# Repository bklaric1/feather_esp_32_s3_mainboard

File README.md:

# feather_esp_32_s3_mainboard

## PCBs for a project at Technical University of Applied Science Augsburg

### Explanation
This repo contains the KiCad 8 files for the main board and the daughter board of the project.  
Necessary files are located in the source folders with the corresponding names, whilst the 3D-models, symbols and footprints can be found in the models, symbols, and footprints folders.  
The rules files are located in the source folders, and correspond with the [2 Layer HD Design Rules](https://community.aisler.net/t/2-layer-hd-design-rules/3732) from Aisler DE.  
The BOM files are located in the source folders in the *bom* folder. They are created using [Interactive HTML Bom](https://github.com/openscopeproject/InteractiveHtmlBom) Plugin. To view the BOM file, clone the repo and open them locally.  
The idea of the design is to make a battery powered system with [Adafruit ESP32-S3 Feather](https://www.adafruit.com/product/5477) as the microcontroller to control the e-paper display. We used the [7.5 inch tri-color electronic paper display](https://www.good-display.com/product/394.html) with the partial refresh as our e-paper display, but any e-paper display from [Good Display](https://www.good-display.com) and from [Waveshare](https://www.waveshare.com) would work, as there is an integrated 3.3V to 5V Boost-Converter which can be turned on if needed (per switch).  
The system is made up from two main PCBs, one that houses the microcontroller and the other which serves as a front panel Board for the buttons.  
All the parts, except the microcontroller, are sponsored by Würth Elektronik. Many thanks to them, as without them sponsoring the parts, the production of the boards would be too expensive for a student project.  
The case for the display, PCBs, and the battery pack are all designed by us and 3D printed.  

### Mainboard
The main board houses the already mentioned Adafruit ESP32-S3 Feather microcontroller. We used the version with 4 MB Flash and 2 MB PSRAM, as we needed the RAM to store a part of firmware on it (static images). The pinout is the same as some other version, so the PCB Design can be used with them as well.  
As already mentioned, there is a 3.3V to 5V Boost-Converter implemented on the board. It is found in the configuration provided by the Würth Elektronik. To switch the output voltage on the display's voltage pin, one needs to only move the switch in another position, as labeled on the board.  
The pinout for the display connector corresponds to the two display manufactures I mentioned above, but check the pinouts before connecting.  
The connector for the board is the connector that links the two boards together.  
Implementation of the external reset button isn't fully finished, but rather left as two pins on the board. I wasn't sure if we'll need to move the reset button somewhere more accessible, so I left it like that. There is no need for another reset button on the board because the microcontroller already features a built-in reset button.  
I also brought the IIC pins out on the board, in case a sensor is need later. These pins are already used internally for the battery monitoring through the MAX17048 chip.  
The battery connection is found directly on the microcontroller module. It is the JST 2-PH plug.  
The microSD adapter is designed by the specification of the espressif themselves, according to their [README](https://github.com/espressif/esp-idf/blob/master/examples/storage/sd_card/sdmmc/README.md). I also fully modified the design to make it possible to switch from the 4-wire connection (SD mode) to the 1-wire connection (SPI), in case we need more GPIO pins for something else.

### Daugtherboard
The design of the daughter board is very simple. It only includes the four buttons with the debouncing design respectively. 
The connector links with the main board to make the system complete.
Board only has one mounting hole, because of the maximum length constrains. We designed the plugin spot for the board on one side, similar to the M.2 SSD mounting technology.

### Battery Pack
As we needed to build a battery powered system, we researched and put together a battery pack with 10 600 mAh and the nominal voltage of 3.7V (4.2V) fully charged.  
The battery pack consists of two 21700 Li-Ion batteries. We have chosen [these](https://www.akkuteile.de/lithium-ionen-akkus/21700/bak/bak-n21700cd-53e-mit-5300mah-10a-3-6v-3-7v-li-ionen-akku_100625_3323) because of the high capacity and small form factor.  
Though any combination of the batteries would work, we decided to maximize the space we have in the case and the budget of our project. That is why we selected these specific cells.  
We also included the already developed [BMS](https://www.akkuteile.de/1s-pcb-keeppower-xzd-1s5530-schutzelektronik-7a_200501_1407) (Battery Management System) PCB to protect the batteries of the deep discharge, overcharge and short circuit.

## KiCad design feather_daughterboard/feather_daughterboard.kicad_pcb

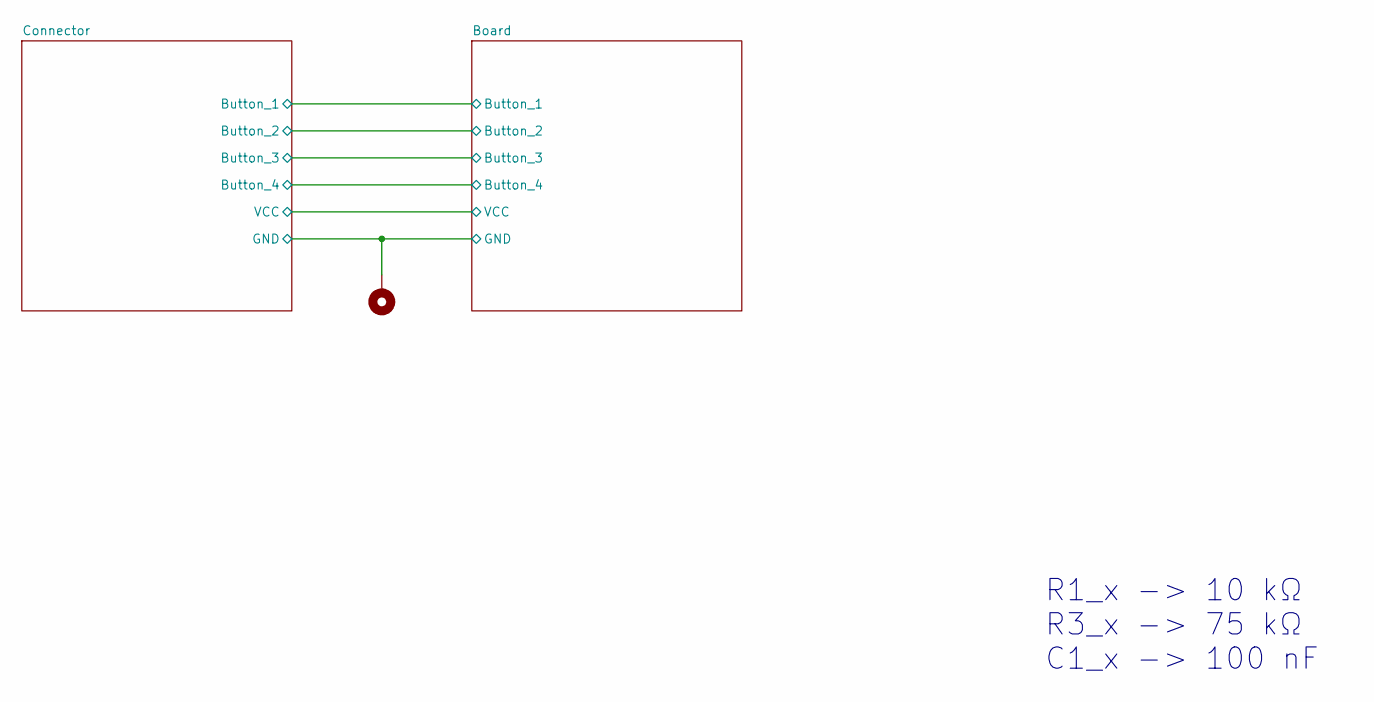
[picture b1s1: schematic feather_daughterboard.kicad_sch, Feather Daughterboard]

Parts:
H2: MountingHole_Pad; MountingHole_2.2mm_M2_DIN965_Pad

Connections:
/Board/GND: H2.1; also elsewhere on the board

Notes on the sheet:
R1_x -> 10 kΩ R3_x -> 75 kΩ C1_x -> 100 nF

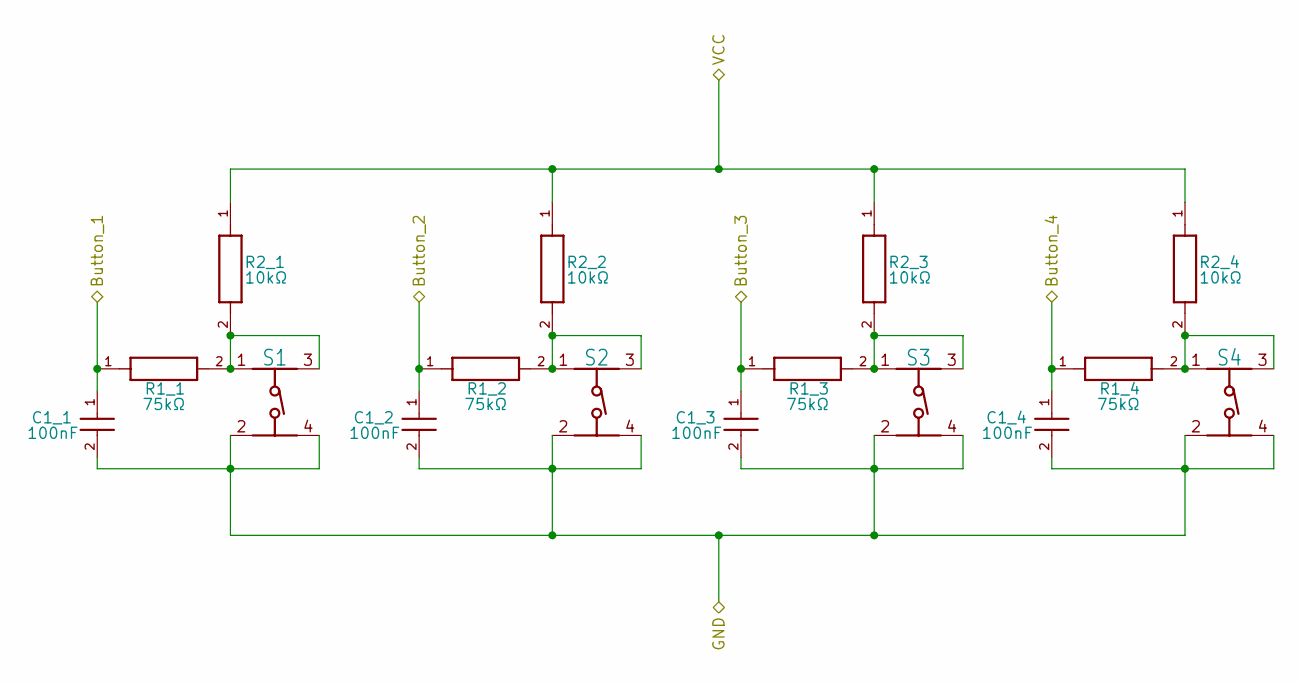
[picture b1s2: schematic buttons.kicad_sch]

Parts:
C1_1, C1_2, C1_3, C1_4: 100nF; WCAP-CSGP_0603_R
R1_1, R1_2, R1_3, R1_4: 75kΩ; WRIS-RSKS_0603_REFLOW
R2_1, R2_2, R2_3, R2_4: 10kΩ; WRIS-RSKS_0603_REFLOW
S1, S2, S3, S4: 430182050816

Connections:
/Board/Button_1: C1_1.1, R1_1.1; also elsewhere on the board
/Board/Button_2: C1_2.1, R1_2.1; also elsewhere on the board
/Board/Button_3: C1_3.1, R1_3.1; also elsewhere on the board
/Board/Button_4: C1_4.1, R1_4.1; also elsewhere on the board
/Board/GND: C1_1.2, C1_2.2, C1_3.2, C1_4.2, S1.2, S1.4, S2.2, S2.4, S3.2, S3.4, S4.2, S4.4; also elsewhere on the board
/Board/VCC: R2_1.1, R2_2.1, R2_3.1, R2_4.1; also elsewhere on the board
unnamed: R1_1.2, R2_1.2, S1.1, S1.3
unnamed: R1_2.2, R2_2.2, S2.1, S2.3
unnamed: R1_3.2, R2_3.2, S3.1, S3.3
unnamed: R1_4.2, R2_4.2, S4.1, S4.3

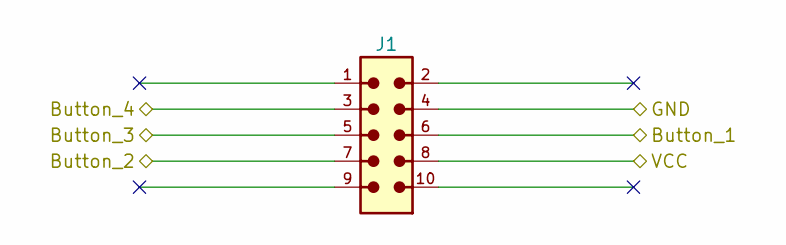
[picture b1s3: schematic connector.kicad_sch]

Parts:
J1: 6250XX21721_62501021721; 62501021721; PART-NUMBER 62501021721

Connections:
/Board/Button_1: J1.6; also elsewhere on the board
/Board/Button_2: J1.7; also elsewhere on the board
/Board/Button_3: J1.5; also elsewhere on the board
/Board/Button_4: J1.3; also elsewhere on the board
/Board/GND: J1.4; also elsewhere on the board
/Board/VCC: J1.8; also elsewhere on the board

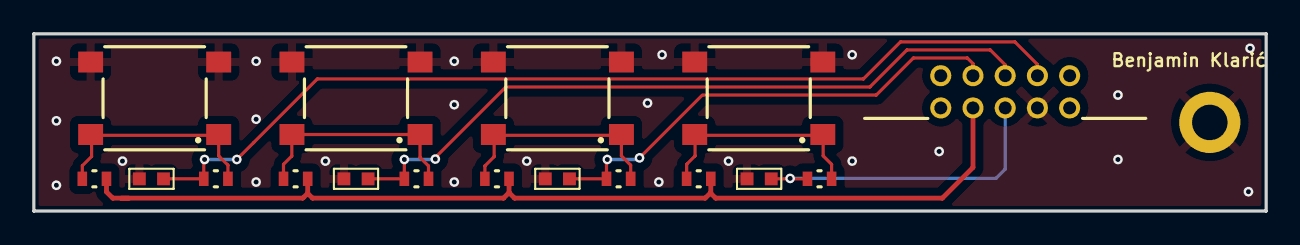
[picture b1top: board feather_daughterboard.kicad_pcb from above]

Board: 2 copper layers, 76.5 x 11.0 mm, 18 parts (0 on the bottom side), 10 nets.

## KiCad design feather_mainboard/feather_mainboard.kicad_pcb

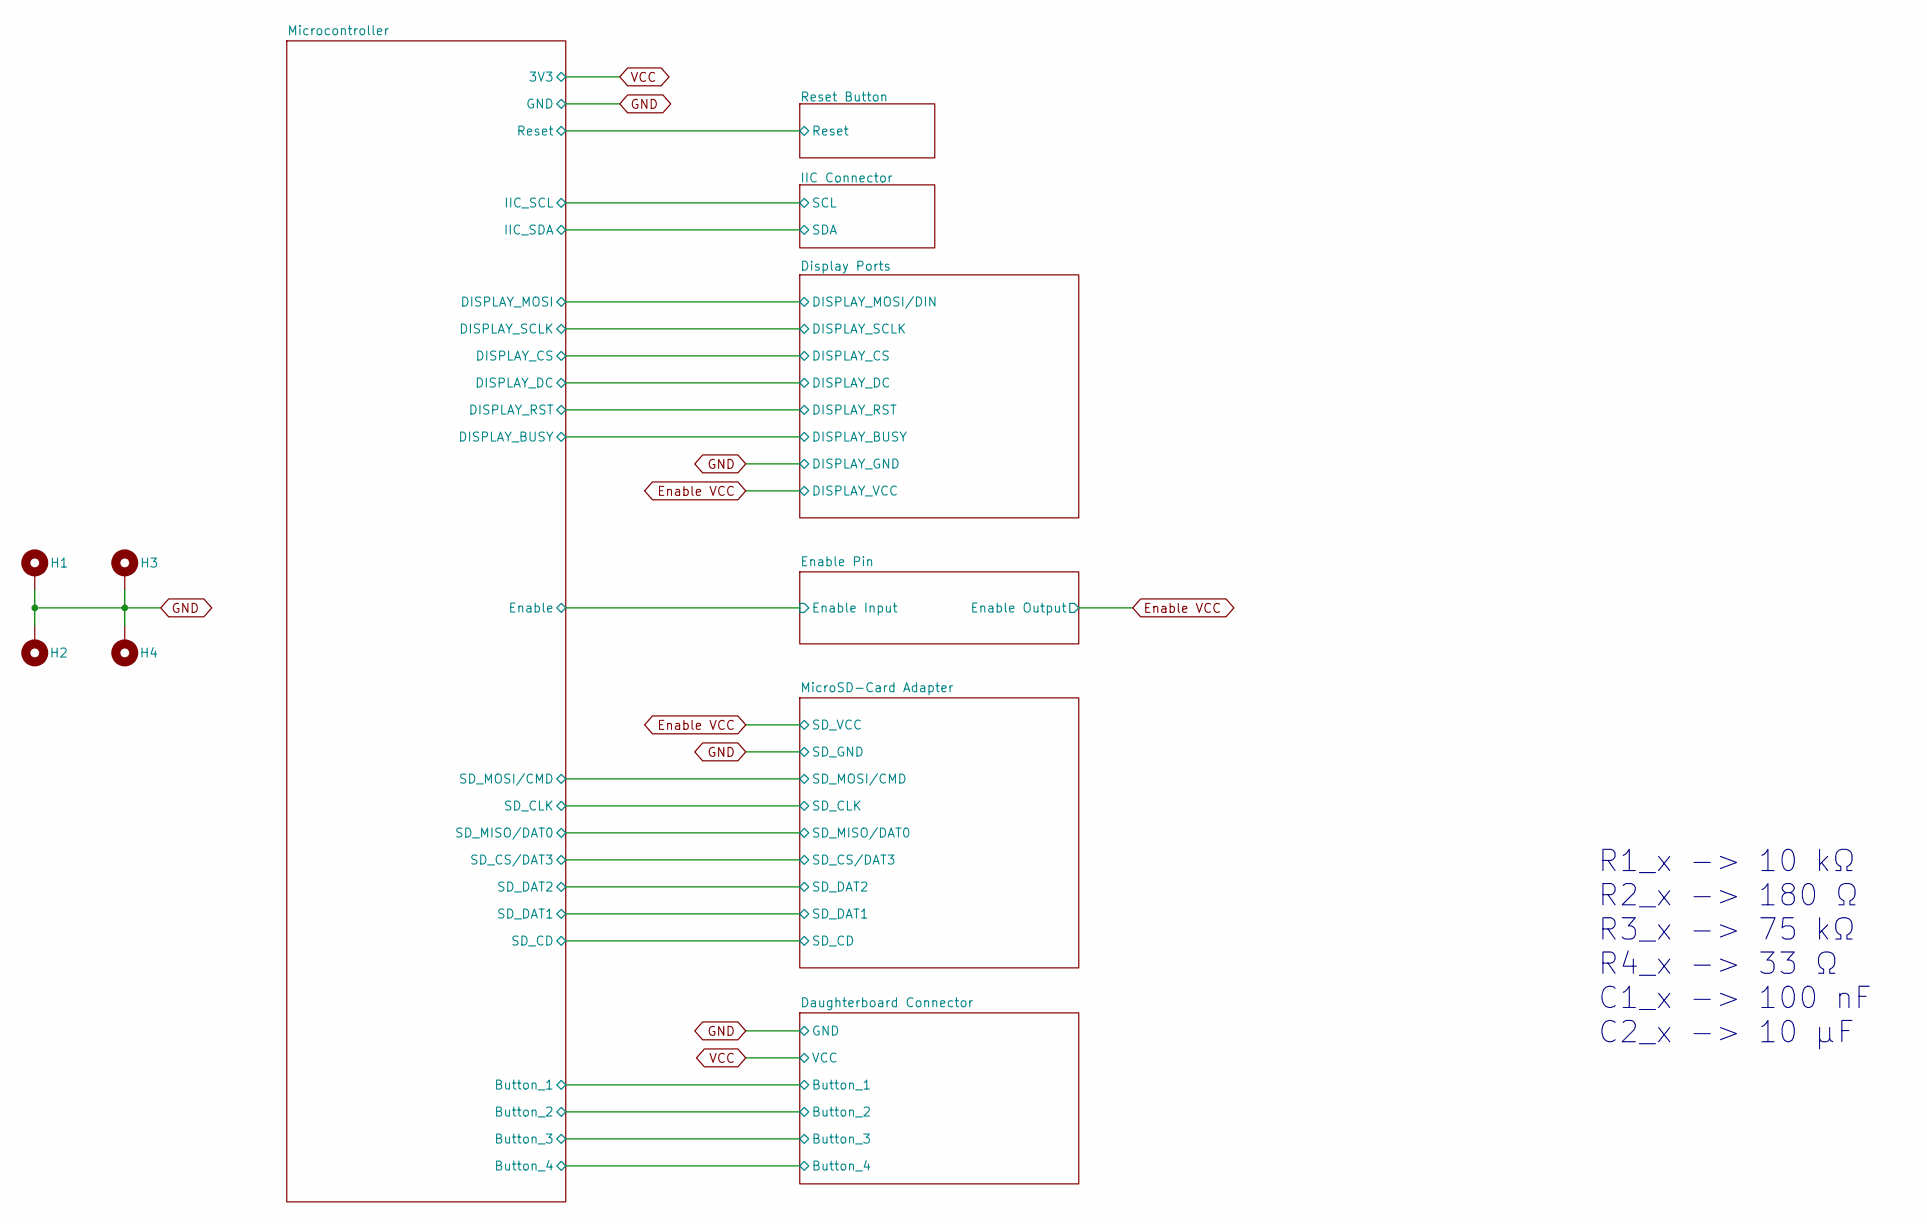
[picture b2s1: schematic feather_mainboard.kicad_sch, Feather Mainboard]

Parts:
H1, H2, H3, H4: MountingHole_Pad; MountingHole_2.2mm_M2_DIN965_Pad

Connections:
GND: H1.1, H2.1, H3.1, H4.1; also elsewhere on the board

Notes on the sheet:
R1_x -> 10 kΩ R2_x -> 180 Ω R3_x -> 75 kΩ R4_x -> 33 Ω C1_x -> 100 nF C2_x -> 10 µF

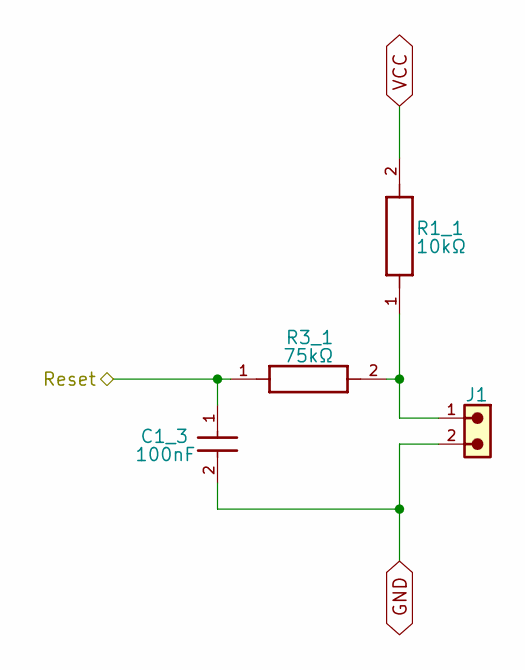
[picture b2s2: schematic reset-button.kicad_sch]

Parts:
C1_3: 100nF; WCAP-CSGP_0603_R
J1: 61300211121; PART-NUMBER 61300211121
R1_1: 10kΩ; WRIS-RSKS_0603_REFLOW
R3_1: 75kΩ; WRIS-RSKS_0603_REFLOW

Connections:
/Microcontroller/Reset: C1_3.1, R3_1.1; also elsewhere on the board
GND: C1_3.2, J1.2; also elsewhere on the board
unnamed: J1.1, R1_1.1, R3_1.2
VCC: R1_1.2; also elsewhere on the board

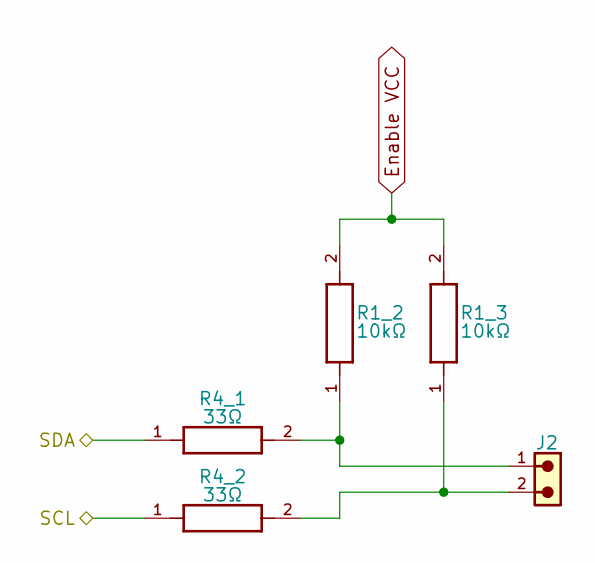
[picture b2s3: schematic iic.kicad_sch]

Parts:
J2: 61300211121; PART-NUMBER 61300211121
R1_2, R1_3: 10kΩ; WRIS-RSKS_0603_REFLOW
R4_1, R4_2: 33Ω; WRIS-RSKS_0603_REFLOW

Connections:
/IIC Connector/SCL: R4_2.1; also elsewhere on the board
/IIC Connector/SDA: R4_1.1; also elsewhere on the board
Enable VCC: R1_2.2, R1_3.2; also elsewhere on the board
unnamed: J2.1, R1_2.1, R4_1.2
unnamed: J2.2, R1_3.1, R4_2.2

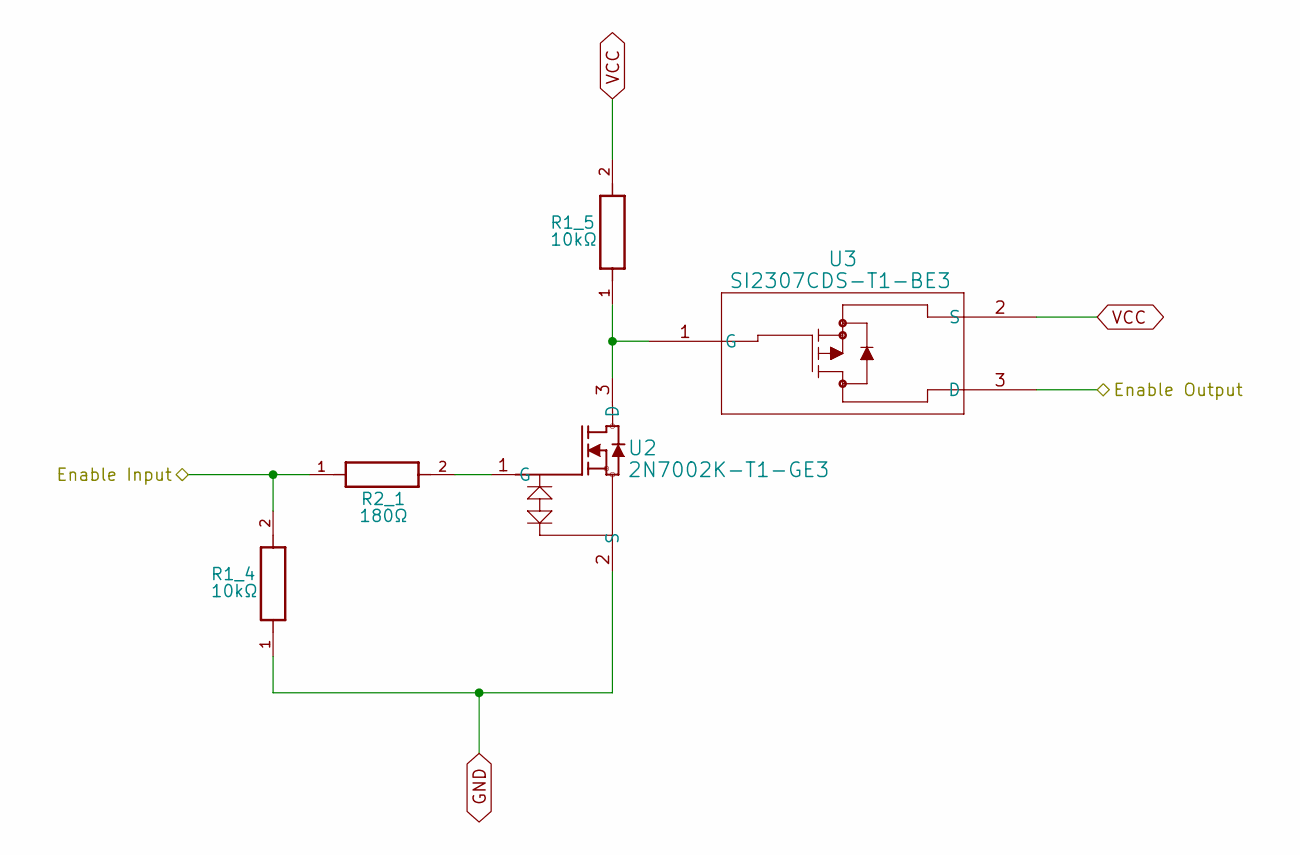
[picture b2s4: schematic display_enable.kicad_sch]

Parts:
R1_4, R1_5: 10kΩ; WRIS-RSKS_0603_REFLOW
R2_1: 180Ω; WRIS-RSKS_0603_REFLOW
U2: 2N7002K-T1-GE3; SOT_02K-T1-GE3_VIS
U3: SI2307CDS-T1-BE3; SOT-23_VIS

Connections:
/Enable Pin/Enable Input: R1_4.2, R2_1.1; also elsewhere on the board
Enable VCC: U3.3 (D); also elsewhere on the board
GND: R1_4.1, U2.2 (S); also elsewhere on the board
unnamed: R1_5.1, U2.3 (D), U3.1 (G)
unnamed: R2_1.2, U2.1 (G)
VCC: R1_5.2, U3.2 (S); also elsewhere on the board

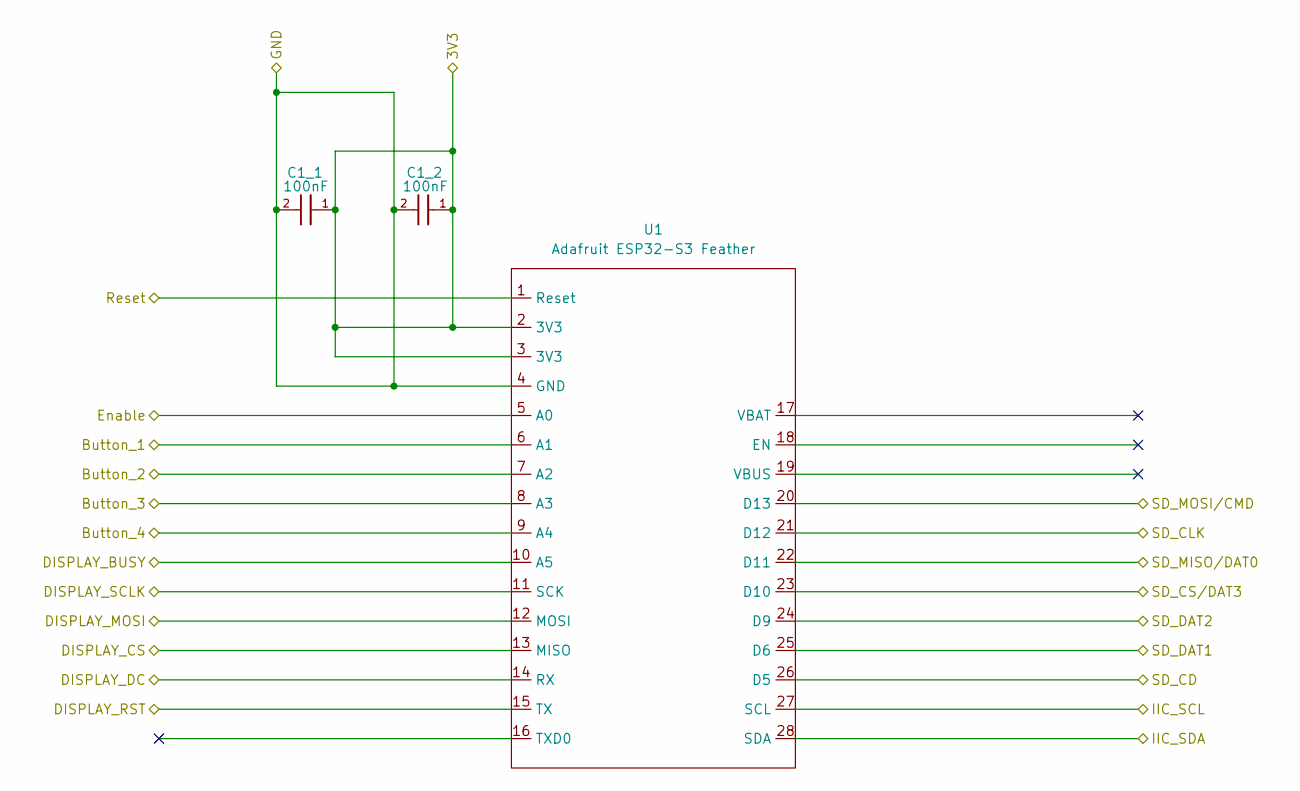
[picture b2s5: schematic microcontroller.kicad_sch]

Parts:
C1_1, C1_2: 100nF; WCAP-CSGP_0603_R
U1: Adafruit ESP32-S3 Feather; Adafruit ESP32-S3 Feather 4MB Flash 2MB PSRAM

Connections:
/Daughterboard Connector/Button_1: U1.6 (A1); also elsewhere on the board
/Daughterboard Connector/Button_2: U1.7 (A2); also elsewhere on the board
/Daughterboard Connector/Button_3: U1.8 (A3); also elsewhere on the board
/Daughterboard Connector/Button_4: U1.9 (A4); also elsewhere on the board
/Display Ports/DISPLAY_BUSY: U1.10 (A5); also elsewhere on the board
/Display Ports/DISPLAY_CS: U1.13 (MISO); also elsewhere on the board
/Display Ports/DISPLAY_DC: U1.14 (RX); also elsewhere on the board
/Display Ports/DISPLAY_MOSI/DIN: U1.12 (MOSI); also elsewhere on the board
/Display Ports/DISPLAY_RST: U1.15 (TX); also elsewhere on the board
/Display Ports/DISPLAY_SCLK: U1.11 (SCK); also elsewhere on the board
/Enable Pin/Enable Input: U1.5 (A0); also elsewhere on the board
/IIC Connector/SCL: U1.27 (SCL); also elsewhere on the board
/IIC Connector/SDA: U1.28 (SDA); also elsewhere on the board
/MicroSD-Card Adapter/SD_CD: U1.26 (D5); also elsewhere on the board
/MicroSD-Card Adapter/SD_CLK: U1.21 (D12); also elsewhere on the board
/MicroSD-Card Adapter/SD_CS/DAT3: U1.23 (D10); also elsewhere on the board
/MicroSD-Card Adapter/SD_DAT1: U1.25 (D6); also elsewhere on the board
/MicroSD-Card Adapter/SD_DAT2: U1.24 (D9); also elsewhere on the board
/MicroSD-Card Adapter/SD_MISO/DAT0: U1.22 (D11); also elsewhere on the board
/MicroSD-Card Adapter/SD_MOSI/CMD: U1.20 (D13); also elsewhere on the board
/Microcontroller/Reset: U1.1 (Reset); also elsewhere on the board
GND: C1_1.2, C1_2.2, U1.4 (GND); also elsewhere on the board
VCC: C1_1.1, C1_2.1, U1.2 (3V3), U1.3 (3V3); also elsewhere on the board

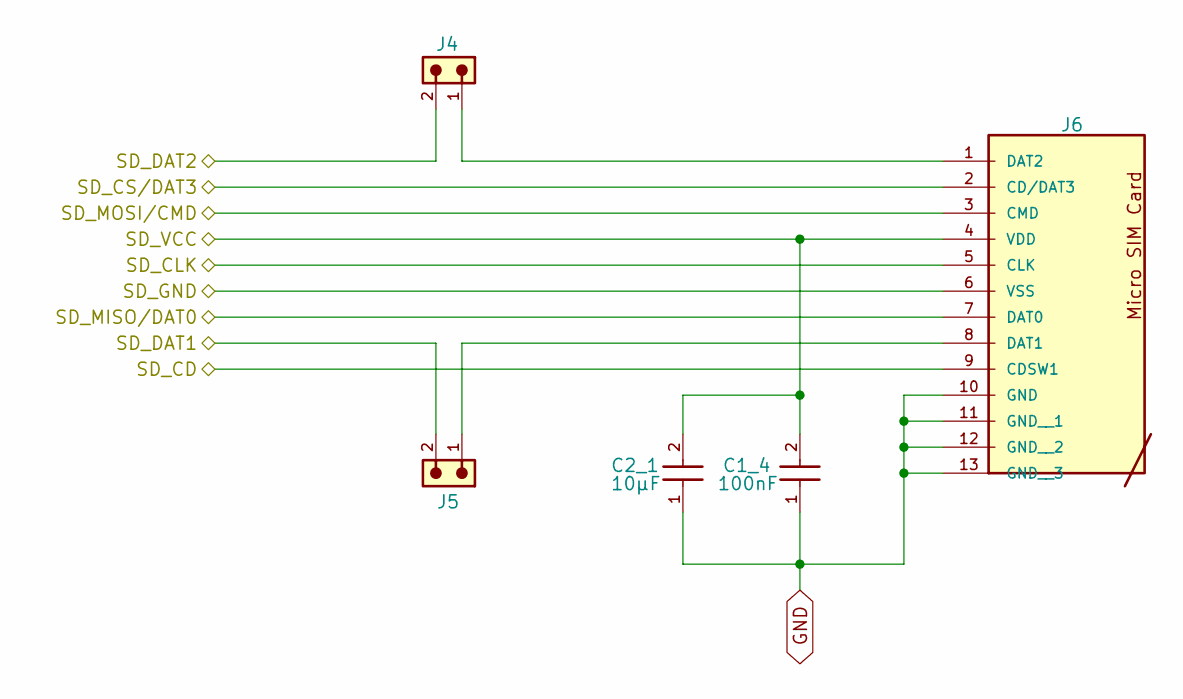
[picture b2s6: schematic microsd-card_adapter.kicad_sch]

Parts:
C1_4: 100nF; WCAP-CSGP_0603_R
C2_1: 10µF; WCAP-CSGP_0603_R
J4, J5: 61300211121; PART-NUMBER 61300211121
J6: 693071020811; PART-NUMBER 693071020811

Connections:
/MicroSD-Card Adapter/SD_CD: J6.9 (CDSW1); also elsewhere on the board
/MicroSD-Card Adapter/SD_CLK: J6.5 (CLK); also elsewhere on the board
/MicroSD-Card Adapter/SD_CS/DAT3: J6.2 (CD/DAT3); also elsewhere on the board
/MicroSD-Card Adapter/SD_DAT1: J5.2; also elsewhere on the board
/MicroSD-Card Adapter/SD_DAT2: J4.2; also elsewhere on the board
/MicroSD-Card Adapter/SD_MISO/DAT0: J6.7 (DAT0); also elsewhere on the board
/MicroSD-Card Adapter/SD_MOSI/CMD: J6.3 (CMD); also elsewhere on the board
Enable VCC: C1_4.2, C2_1.2, J6.4 (VDD); also elsewhere on the board
GND: C1_4.1, C2_1.1, J6.6 (VSS), J6.10 (GND), J6.11 (GND__1), J6.12 (GND__2), J6.13 (GND__3); also elsewhere on the board
unnamed: J5.1, J6.8 (DAT1)
unnamed: J4.1, J6.1 (DAT2)

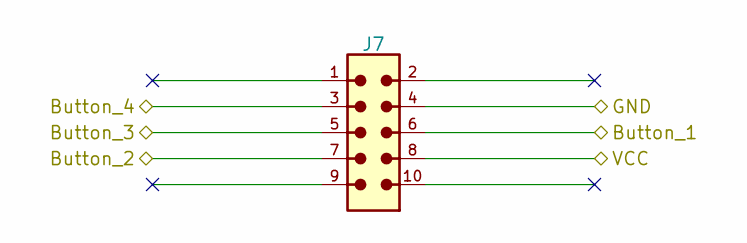
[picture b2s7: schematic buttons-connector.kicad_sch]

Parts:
J7: 62501021721; 62501021721_full; PART-NUMBER 62501021721

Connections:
/Daughterboard Connector/Button_1: J7.6; also elsewhere on the board
/Daughterboard Connector/Button_2: J7.7; also elsewhere on the board
/Daughterboard Connector/Button_3: J7.5; also elsewhere on the board
/Daughterboard Connector/Button_4: J7.3; also elsewhere on the board
GND: J7.4; also elsewhere on the board
VCC: J7.8; also elsewhere on the board

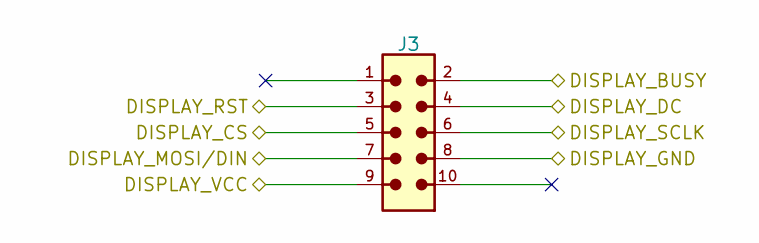
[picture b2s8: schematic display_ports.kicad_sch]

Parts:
J3: 62501021721; 62501021721_full; PART-NUMBER 62501021721

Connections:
/Display Ports/DISPLAY_BUSY: J3.2; also elsewhere on the board
/Display Ports/DISPLAY_CS: J3.5; also elsewhere on the board
/Display Ports/DISPLAY_DC: J3.4; also elsewhere on the board
/Display Ports/DISPLAY_MOSI/DIN: J3.7; also elsewhere on the board
/Display Ports/DISPLAY_RST: J3.3; also elsewhere on the board
/Display Ports/DISPLAY_SCLK: J3.6; also elsewhere on the board
Enable VCC: J3.9; also elsewhere on the board
GND: J3.8; also elsewhere on the board

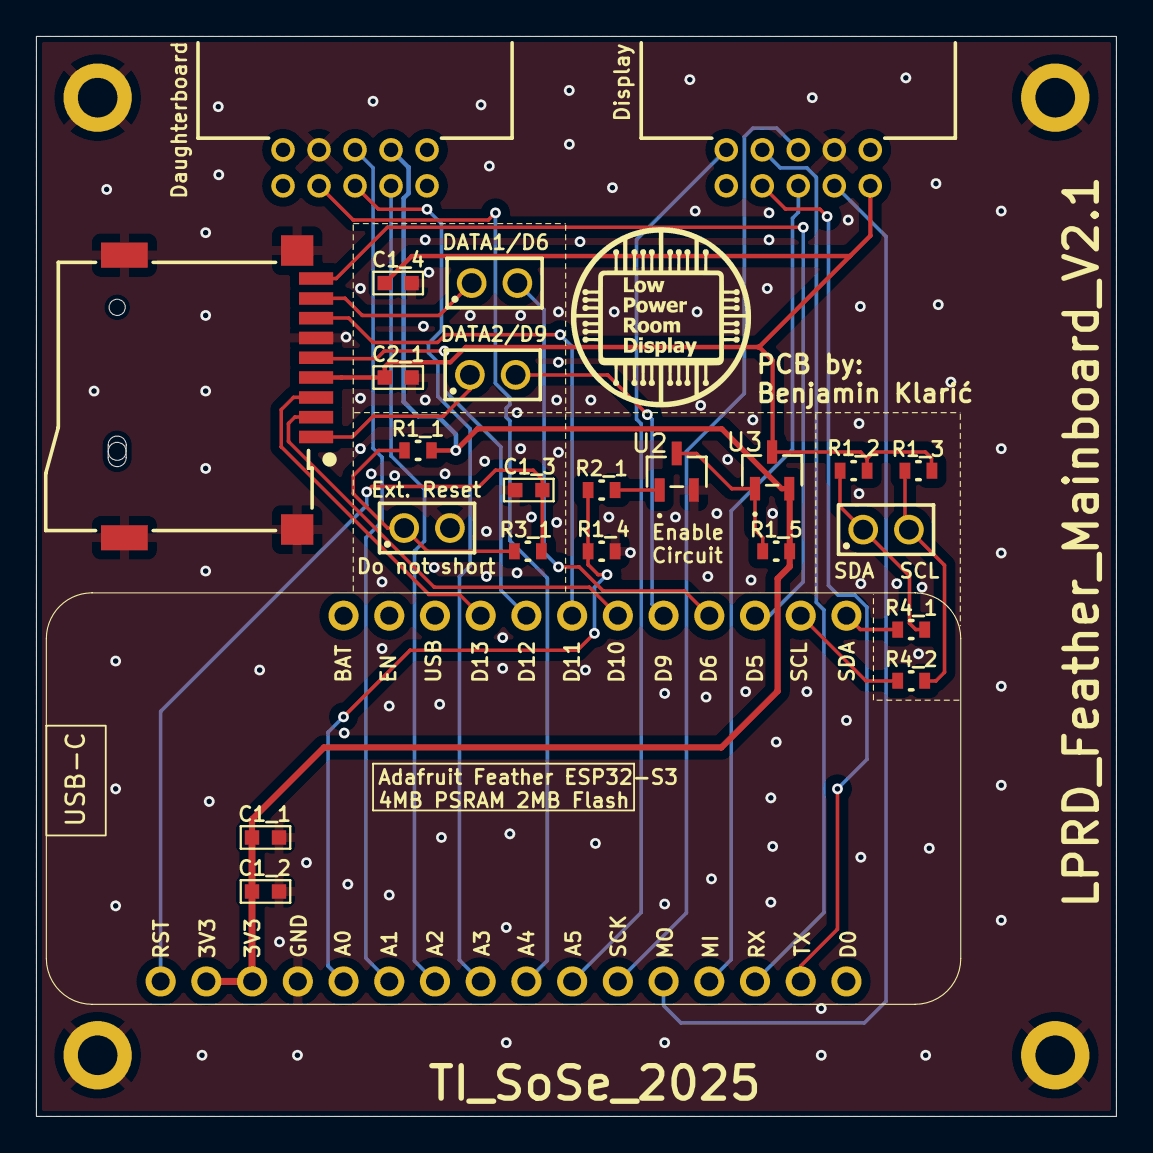
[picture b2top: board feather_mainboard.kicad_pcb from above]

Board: 2 copper layers, 60.0 x 60.0 mm, 28 parts (0 on the bottom side), 31 nets.

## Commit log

2024-10-16 added parts of the schematics that were already used by the xiao_mainboard, as we want to be as backwards compatible as possible
2024-10-19 finished microcontroller and microsd card subsheets. TODO: button subsheets and internal connections
2024-10-20 schematic is almost done (check TODOs in schematic file)
2024-10-20 changed footprints location to match the new folder. TODO: check if the path is working on another computer
2024-10-24 added daughter board
2024-10-25 finished daughter board
2024-10-26 finished mainboard design, need to do the routing
2024-10-26 finished the mainboard, added bom files
2024-10-27 moved the logo and did some small changes
2024-10-27 added pins for the sd connections
2024-10-28 changed the connector on the daughter board
2024-10-28 finished mainboard and daughterboard
2024-10-29 added bigger logo and labeled the pins on the connectors
2024-10-29 added logo files
2024-12-12 Corrected/switched the names of MISO and MOSI pins
2025-02-04 Added V1.1: added a Shottky diode to block the parasitic feedback into the system from the SD adapter; routed the SD adapter pull-ups to the SD Vcc and not the uC Vcc; updated silkscreen text; cleane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
2025-02-05 Small changes to silkscreen text
2025-02-05 Small changed to daughterboard silkscreen text
2025-02-05 Removed the diode, since it is not needed
2025-02-05 Removed diode files, as they are no longer needed
2025-02-05 Updated silkscreen text
2025-04-21 Updated the mainboard: removed unnecessary pull-ups on SD card lines; connected IIC pull-ups to enable circuit; cleaned up schematic
2025-04-21 Updated BOM and README
2025-04-21 Updated Daughterboard and added Gerber files
2025-04-22 Small chanegs to Daughterboard; updated jlc export
2025-04-23 Updated jlc export of the mainboard
